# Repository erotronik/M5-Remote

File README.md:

# M5 REMOTE

Please note that this is a modification of the OSSM-M5-Remote project by Ortlof, which is available at [https://github.com/ortlof/OSSM-M5-Remote](https://github.com/ortlof/OSSM-M5-Remote).

Also note that this is an early prototype that is not tested.

This modified project adds RGB Rotary encoders that can light the knobs, and allows the installation of an LED in the push-button.

Furthermore, communication with the board is switched to I2C, using a PWM controller for the LEDs and a port expander for the Rotary encoders. Note that this means that this modification is *not compatible* with the software written for the original OSSM M5 Remote. Currently, there only is a skeleton project [that sketches how to interface with the components on the board in the Firmware folder](./Firmware).

The modified PCB design can be found in the `Hardware/PCB` folder.

The remaining folders in this project are unchanged - please note that the software contained in this repository will not work with the changed hardware.

## Overview of the M5-Remote

The M5 Remote is a remote control platform, e.g. for Sex Toys, or estim devices.

The original project was developed for the OSSM project (https://github.com/KinkyMakers/OSSM-hardware).

This modified version currently does not have direct support for any toys, and requires you to write your own software.

To help with development and design join the KinkyMakers Discord: https://discord.gg/MmpT9xE . Be sure to say hello in the #m5-remote channel. 

# Build the M5 Remote Yourself

## PCB from JLCPCB

The PCB is designed to be made using the JLCPCB assembly service.

To order the PCB, go to [JLCPCP](https://jlcpcb.com) and upload the gerber zip contained in `PCB/jlcpcb`. Leave all settings at default - you can change the PCB colour if you want.

Enable "PCB" assembly, and choose "assemble bottom side" (not selected by default).

In the next step, upload `bom.csv` and `positions.csv`. Verify that the positioning of the components looks corerct before ordering.

## Bill Of Materials for sourcing Electrical Components

BOM is on Octopart for Easy Sourcing: https://octopart.com/bom-tool/pqx0O8QI

## Additional parts needed that are not found on Octopart:

Note - instead of the Kailh switches from pimoroni, any Cherry-compatible switch with LED hole can be used.

| Quantity | Part | Sourcing EU | Price € |
|----------|------|-------------|---------|
| 1x | Switch | https://shop.pimoroni.com/products/kailh-mechanical-switches-pack-of-12?variant=32056315314259 | 7
| 2x | M3x25mm Hex Head Cap Bolt | https://www.amazon.de/Edelstahl-Innensechskant-Bolzenset-Eisenrahmen-Mechanischer-Innensechskantschraube-Mutternset/dp/B07PPFT871/ | 12,97 € |
| 4x | M3x20mm Hex Head Cap Bolt | Comes as part of the set mentioned above | " | 
| 4x | Heat Set inserts M3 | https://www.amazon.de/ruthex-Gewindeeinsatz-St%C3%BCck-Gewindebuchsen-Kunststoffteile/dp/B08BCRZZS3 | 8,99 € |
| 1x | 3,7v 2000mAh Lipo Batterie Size 34,5 mm x 10,6 mm x 56 mm | https://www.amazon.de/EEMB-103454-2AhLithium-Schutzplatine-Isolationsbeschichtung/dp/B08214DJLJ/ | 14,89 € |

--------------------------------------------

| Quantity | Part | Sourcing US | Price $ |
|----------|------|-------------|---------|
| 2x | M3x25mm Hex Head Cap Bolt | https://www.amazon.com/dp/B09NR8X2LV | $17.99 |
| 4x | M3x20mm Hex Head Cap Bolt | Comes as part of the set mentioned above | " | 
| 4x | Heat Set inserts M3 | https://www.amazon.com/ruthex-M3-Threaded-Inserts-RX-M3x5-7/dp/B08BCRZZS3 | $10.99 |
| 1x | 3.7v 2000mAh Lipo Battery Size 34.5 X 56 X 10.6 mm (The wires will need to be reversed in the connector on this one! See Assembly instructions for more info.) | https://www.amazon.com/EEMB-2000mAh-Battery-Rechargeable-Connector/dp/B08214DJLJ/ | $14.99 |

## 3D Printed Parts Needed:

| Quantity | Part | Information |
|----------|------|-------------|
| 1x | Bottom.stl or Bottom_Adafruit_LIPO.stl or Bottom-Magnets.stl| There is a specific version for the wider Adafruit LIPO battery. Print with the base side facing down, 6 walls 20% Infill | 
| 1x | TOP-*-Keycap-Standoff.stl | Top Depends on your Keycap: Cherry or DSA (DSA is wider) | 
| 4x | M5_Remote_Knob_Customizable.scad | If you go for the 3d Printed knobs |

Filament - A good quality PLA works well. While there are no threads it is recommended that your printer is well calibrated.  

# [Assembly instructions](Assembly.md)

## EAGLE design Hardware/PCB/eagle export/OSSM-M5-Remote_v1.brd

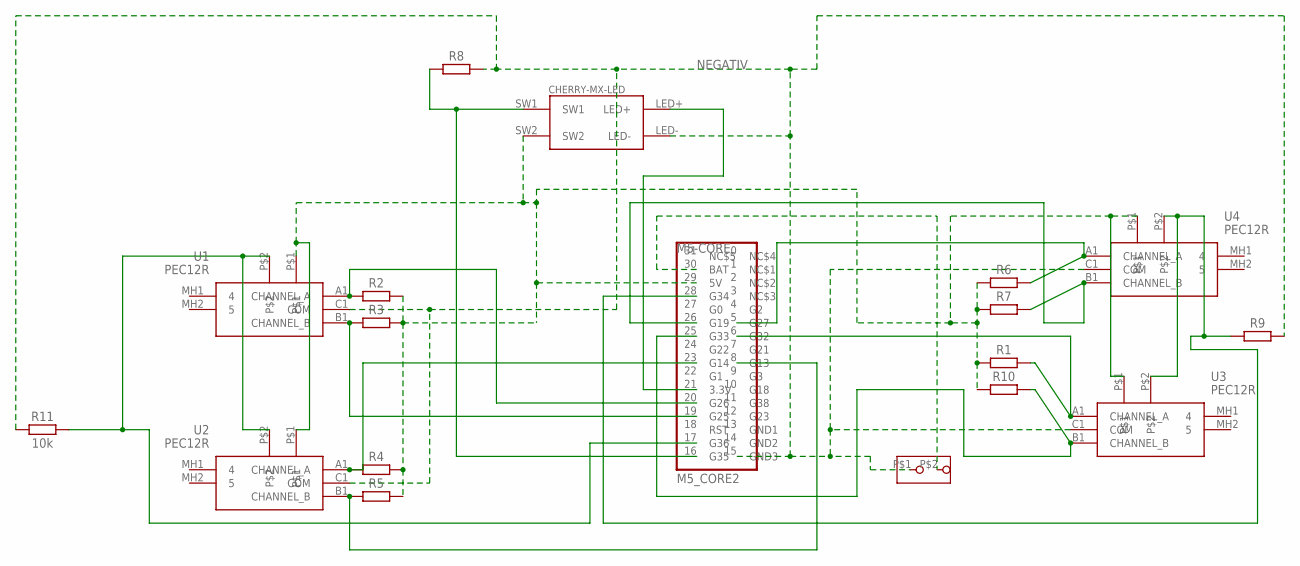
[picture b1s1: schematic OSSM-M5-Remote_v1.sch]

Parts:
M5-CORE: M5_CORE2
R1, R2, R3, R4, R5, R6, R7, R8, R9, R10: R_CHIP-1206(3216-METRIC); RESC3216X70
R11: 10k; RESC3216X70
U1, U2, U3, U4: PEC12R; PEC12R4017FN0024
U$3: JST-PH-2MM,180; JST-PH-2.0MM_180DEGREES
U$4: CHERRY-MX-LED

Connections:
+5V: M5-CORE.29 (5V), R1.1, R2.2, R3.2, R4.2, R5.2, R6.1, R7.1, R10.1, U1.P$1, U2.P$1, U3.P$1, U4.P$1, U$4.SW2
BAT+: M5-CORE.30 (BAT), U$3.P$2
unnamed: M5-CORE.21 (3.3V), U$4.LED+
unnamed: M5-CORE.20 (G26), R2.1, U1.A1 (CHANNEL_A)
unnamed: M5-CORE.19 (G25), R3.1, U1.B1 (CHANNEL_B)
unnamed: M5-CORE.23 (G14), R4.1, U2.A1 (CHANNEL_A)
unnamed: M5-CORE.8 (G13), R5.1, U2.B1 (CHANNEL_B)
unnamed: M5-CORE.5 (G27), R6.2, U4.A1 (CHANNEL_A)
unnamed: M5-CORE.26 (G19), R7.2, U4.B1 (CHANNEL_B)
unnamed: M5-CORE.6 (G32), R1.2, U3.A1 (CHANNEL_A)
unnamed: M5-CORE.25 (G33), R10.2, U3.B1 (CHANNEL_B)
unnamed: M5-CORE.17 (G36), R11.2, U1.P$2, U2.P$2
unnamed: M5-CORE.28 (G34), R9.1, U3.P$2, U4.P$2
unnamed: M5-CORE.16 (G35), R8.1, U$4.SW1
NEGATIV: M5-CORE.15 (GND3), R8.2, R9.2, R11.1, U1.C1 (COM), U2.C1 (COM), U3.C1 (COM), U4.C1 (COM), U$3.P$1, U$4.LED-

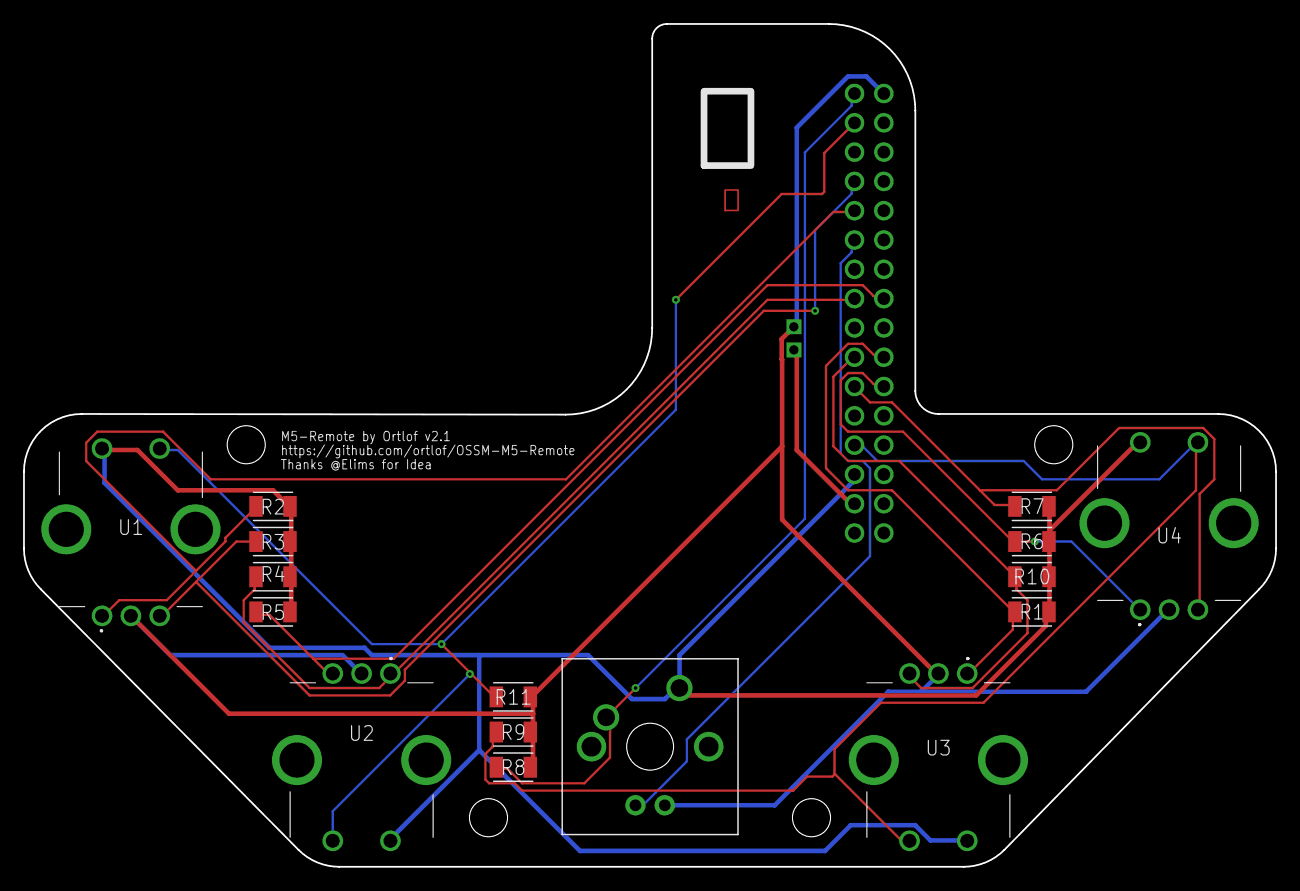
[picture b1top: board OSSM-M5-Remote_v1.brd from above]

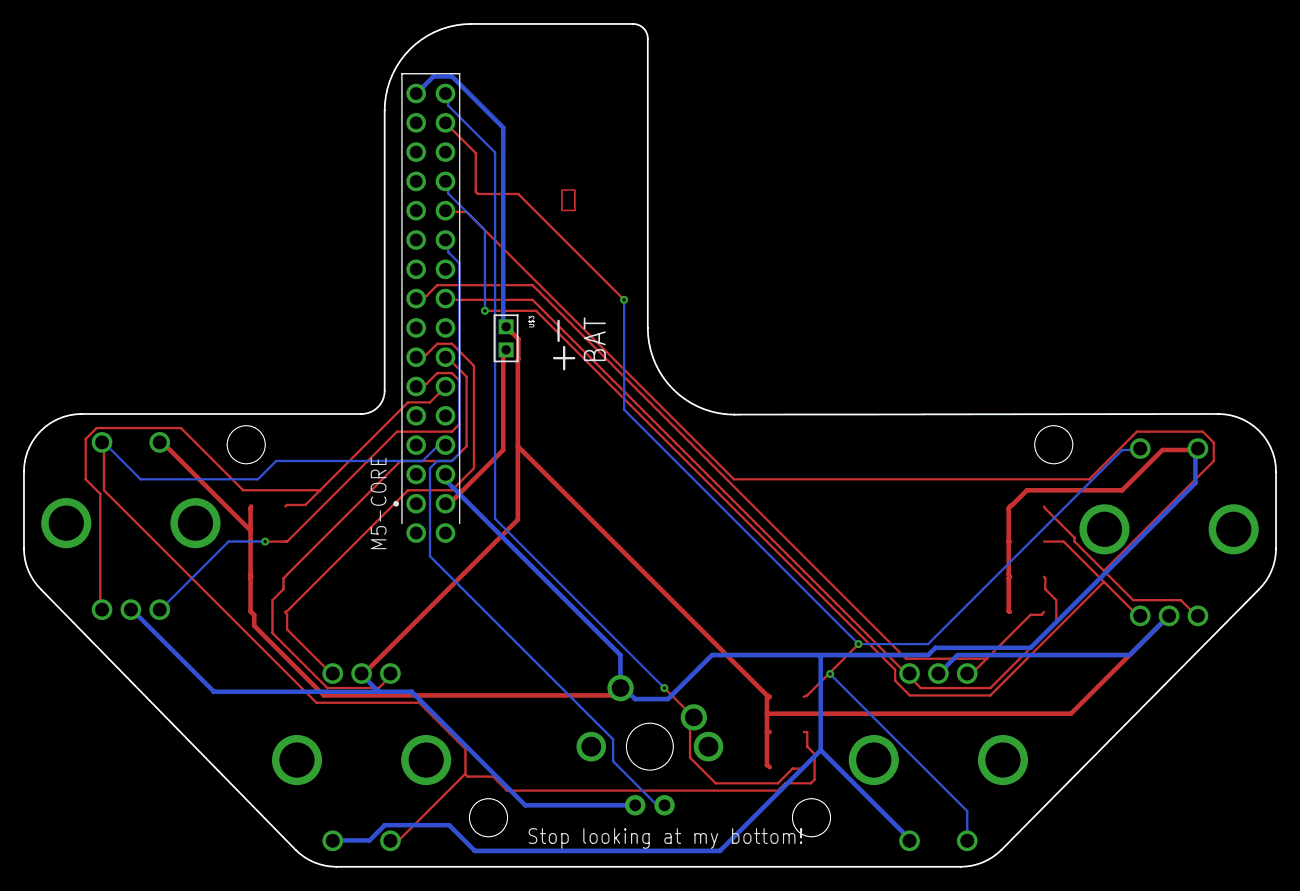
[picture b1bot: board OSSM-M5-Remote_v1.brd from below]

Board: 2 copper layers, 108.5 x 73.1 mm, 18 parts (2 on the bottom side), 15 nets.

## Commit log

2024-02-12 Add current version and eagle exports
2024-02-12 kicad import
2024-02-16 Update schematic, remove traces
2024-03-21 Cleaner schematic
2024-03-22 Starting routing
2024-03-22 Everything connected
2024-03-26 PCB updates
2024-03-26 Big rename
2024-03-27 Final touches for first PCB version
2024-04-22 Tiny fix
2024-04-22 Update readmes
2024-04-22 Remove source
    Does not work with this version of the hardware.
2024-04-23 Add skeleton firmware
2024-04-23 Add some sample code for the CoreS3 and the new hardware
2024-04-23 Don't enable the pullups on the switches for rotary encoders, they are already pull down
2024-04-23 A little cleanup ready to add some encoder handling
2024-04-23 Cleanup. Tell MCP to just mirror the interrupt to both pins so we can ignore one anyway
2024-04-23 Test rotary
2024-04-23 Working with a thread
2024-04-23 Clean up the messy test code
2024-04-23 No need to invert output from switches, remember to clear interrupts
2024-04-26 Add a title and make the scrolling bit smaller
2024-04-26 Debounce time was causing some quick presses to be ignored, reduce it. Fix silly logic to something more simplest
2024-04-26 New remote pic
2024-05-01 Just move the IO m5 stuff to a header file for now to make it easier to include it in other projects, can be made into a library etc later
